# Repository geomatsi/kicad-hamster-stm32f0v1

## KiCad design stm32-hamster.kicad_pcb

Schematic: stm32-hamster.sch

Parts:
BT1: 9V; TerminalBlock_Phoenix_MKDS-1,5-2_1x02_P5.00mm_Horizontal
C1: 220uF; CP_Radial_D8.0mm_P3.80mm
C2: 0.1uF; C_1206_3216Metric_Pad1.42x1.75mm_HandSolder
C3, C4: 470pF; C_1206_3216Metric_Pad1.42x1.75mm_HandSolder
C5, C6: 100uF; CP_Radial_D6.3mm_P2.50mm
D1: PWR; LED_1206_3216Metric_Pad1.42x1.75mm_HandSolder
D2, D3: 1N5818; D_DO-41_SOD81_P10.16mm_Horizontal
J1: SWD; PinHeader_1x04_P2.54mm_Vertical
J2: DIST; PinHeader_1x04_P2.54mm_Vertical
J3, J4: LVL; PinHeader_1x02_P2.54mm_Vertical
JP1: LED; PinHeader_1x02_P2.54mm_Vertical
JP2: PWRSEL; PinHeader_1x03_P2.54mm_Vertical
L1, L2: 220uH; L_Radial_D7.2mm_P3.00mm_MuRATA_1700
Q1: IRLML5203; SOT-23
R1, R3: 10k; R_1206_3216Metric_Pad1.42x1.75mm_HandSolder
R2: 500; R_1206_3216Metric_Pad1.42x1.75mm_HandSolder
R4: 1k; R_1206_3216Metric_Pad1.42x1.75mm_HandSolder
R5: 11k; R_1206_3216Metric_Pad1.42x1.75mm_HandSolder
R6, R7: 0.22; R_1206_3216Metric_Pad1.42x1.75mm_HandSolder
R8: 3k; R_1206_3216Metric_Pad1.42x1.75mm_HandSolder
R9: 18k; R_1206_3216Metric_Pad1.42x1.75mm_HandSolder
R10, R11, R12, R13: 1M; R_1206_3216Metric_Pad1.42x1.75mm_HandSolder
SW1: RST; SW_SPST_REED_CT05-XXXX-J1
U1: DS18B20; TO-92_Inline
U2, U3: MC34063AD; SOIC-8_3.9x4.9mm_P1.27mm
U4: STM32F030F4Px; TSSOP-20_4.4x6.5mm_P0.65mm
U5: NRF24L01_Breakout; nRF24L01_Breakout
U6: LM358; SOIC-8_3.9x4.9mm_P1.27mm

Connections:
+3V3: C6.1, J1.4, J3.1, J4.1, JP2.3, L2.2, R1.1, R9.1, U1.3 (VDD), U4.5, U4.16, U5.2, U6.8 (V+)
+5V: C5.1, JP2.1, L1.2, R8.1
+BATT: BT1.1, Q1.3 (D)
GND: BT1.2, C1.2, C2.2, C3.2, C4.2, C5.2, C6.2, D2.2 (A), D3.2 (A), J1.1, J2.4, Q1.1 (G), R2.2, R3.2, R4.2, R5.2, R11.2, R13.2, SW1.1, U1.1 (GND), U2.4 (GND), U3.4 (GND), U4.15, U5.1, U6.4 (V-)
unnamed: C1.1, Q1.2 (S), R6.2, R7.1, U2.6 (Vin), U3.6 (Vin)
unnamed: C2.1, R1.2, SW1.2, U4.4
unnamed: C3.1, U2.3 (TC)
unnamed: C4.1, U3.3 (TC)
unnamed: D1.1, R2.1
unnamed: D1.2, JP1.1
unnamed: D2.1 (K), L1.1, U2.2 (SwE)
unnamed: D3.1 (K), L2.1, U3.2 (SwE)
unnamed: J1.2, JP1.2, U4.19
unnamed: J1.3, U4.20
unnamed: J2.1, JP2.2
unnamed: J2.2, U4.17
unnamed: J2.3, U4.18
unnamed: J3.2, R10.1
unnamed: J4.2, R12.1
unnamed: R3.1, U4.1
unnamed: R4.1, R8.2, U2.5 (Vfb)
unnamed: R5.1, R9.2, U3.5 (Vfb)
unnamed: R6.1, U2.1 (SwC), U2.7 (Ipk), U2.8 (DC)
unnamed: R7.2, U3.1 (SwC), U3.7 (Ipk), U3.8 (DC)
unnamed: R10.2, R11.1, U6.3 (+)
unnamed: R12.2, R13.1, U6.5 (+)
unnamed: U1.2 (DQ), U4.14
unnamed: U4.6, U6.1, U6.2 (-)
unnamed: U4.7, U6.6 (-), U6.7
unnamed: U4.8, U5.3
unnamed: U4.9, U5.4
unnamed: U4.10, U5.8
unnamed: U4.11, U5.5
unnamed: U4.12, U5.7
unnamed: U4.13, U5.6

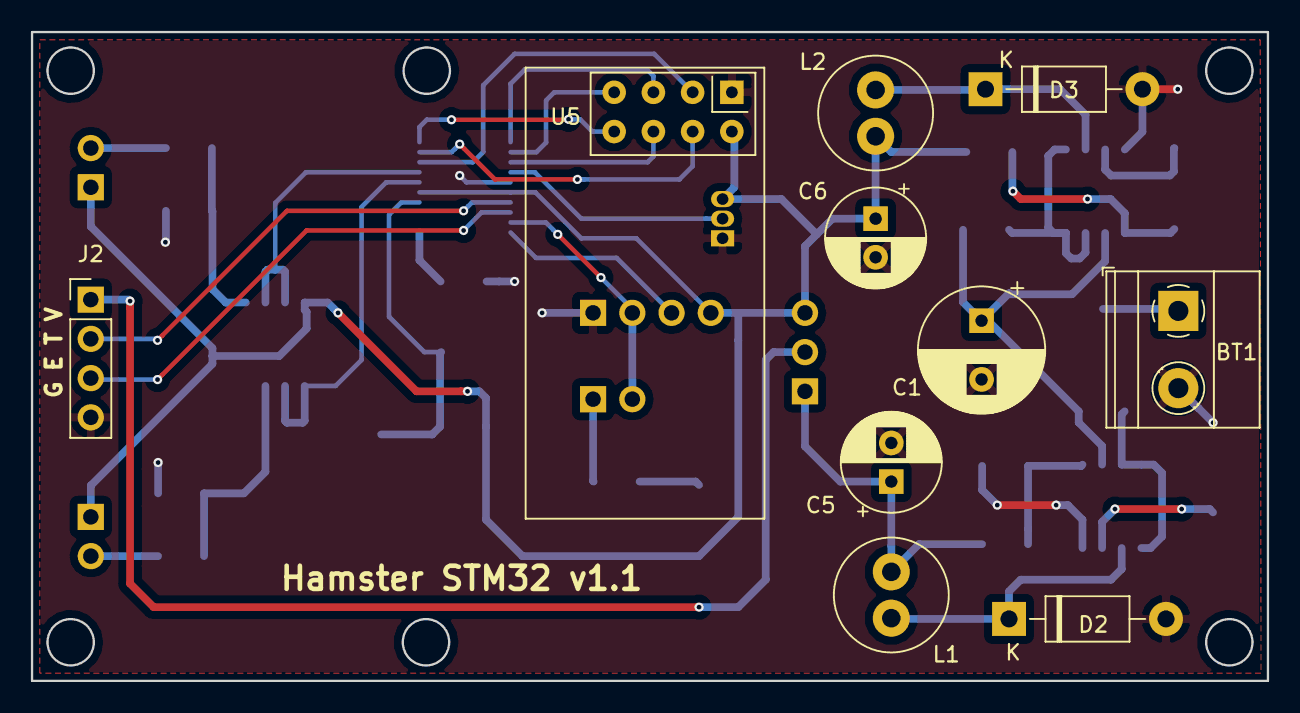
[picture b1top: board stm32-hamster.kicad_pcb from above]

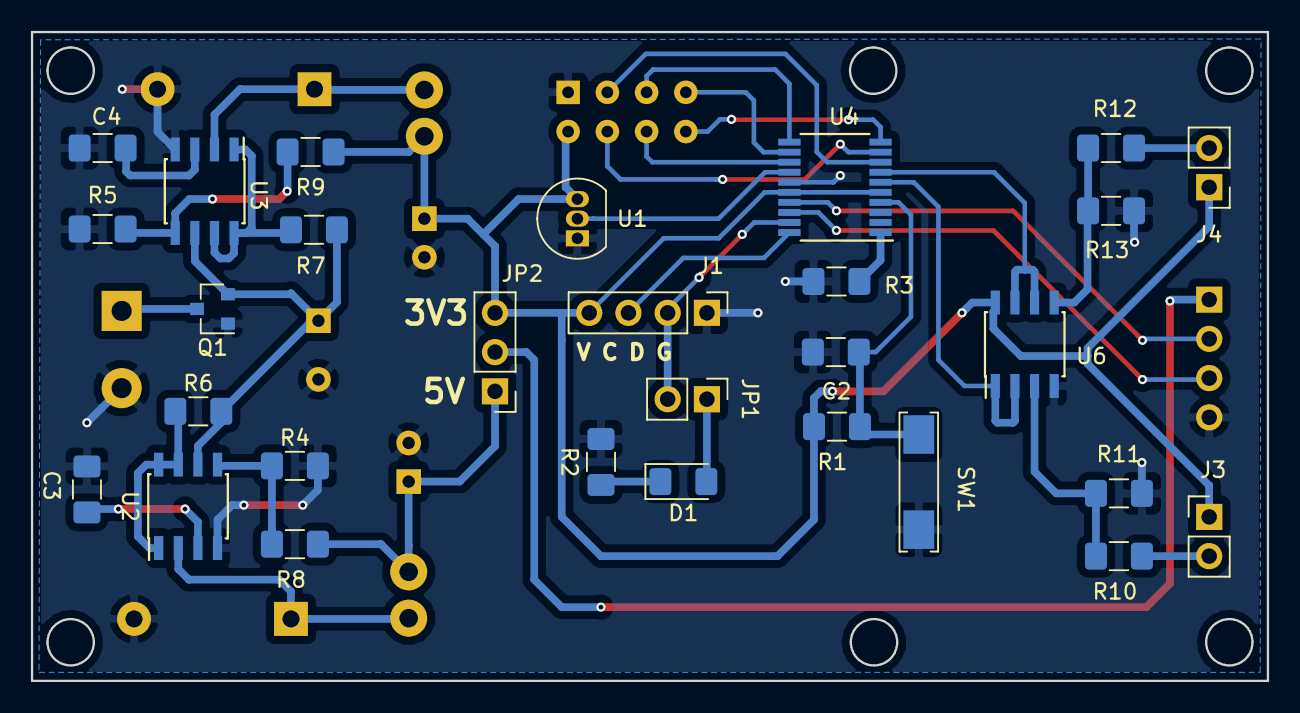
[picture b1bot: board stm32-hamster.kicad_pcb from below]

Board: 2 copper layers, 80.0 x 42.0 mm, 39 parts (29 on the bottom side), 35 nets.

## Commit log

2017-04-01 stm32-hamster: v1 revision
2018-09-15 start over again with kicad v5
    Remove all kicad v4 files, rework project using kicad v5.
2018-09-22 stm32f0v1: kicad5
    - schematics completed
    - footprint selection completed
    - layout completed including marks on F.Silk and B.Silk
    - ready for gerbers
2018-09-22 hamster: stm32f0: generate gerber files
2018-09-22 hamster: stm32f0v1: add device schematics and 3d views
